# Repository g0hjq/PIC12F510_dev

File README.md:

# PIC12F510_dev

A small and simple PCB design for developing circuits using the PIC12F510 and similar 8-Pin PIC processors.
The processor is 8-pin DIL and may be socketed, all other components are 0805 or SOT23 SMD.

Provides:
* 3 high-current outputs, with on-board LED monitors
* 2 protected inputs with capacitor debounce and pull-ups
* Power Supply Reversal protection
* In-circuit Programming Header
* Access to all PIC Pins

If you don't need all the output or input buffers, there is no need to populate the components

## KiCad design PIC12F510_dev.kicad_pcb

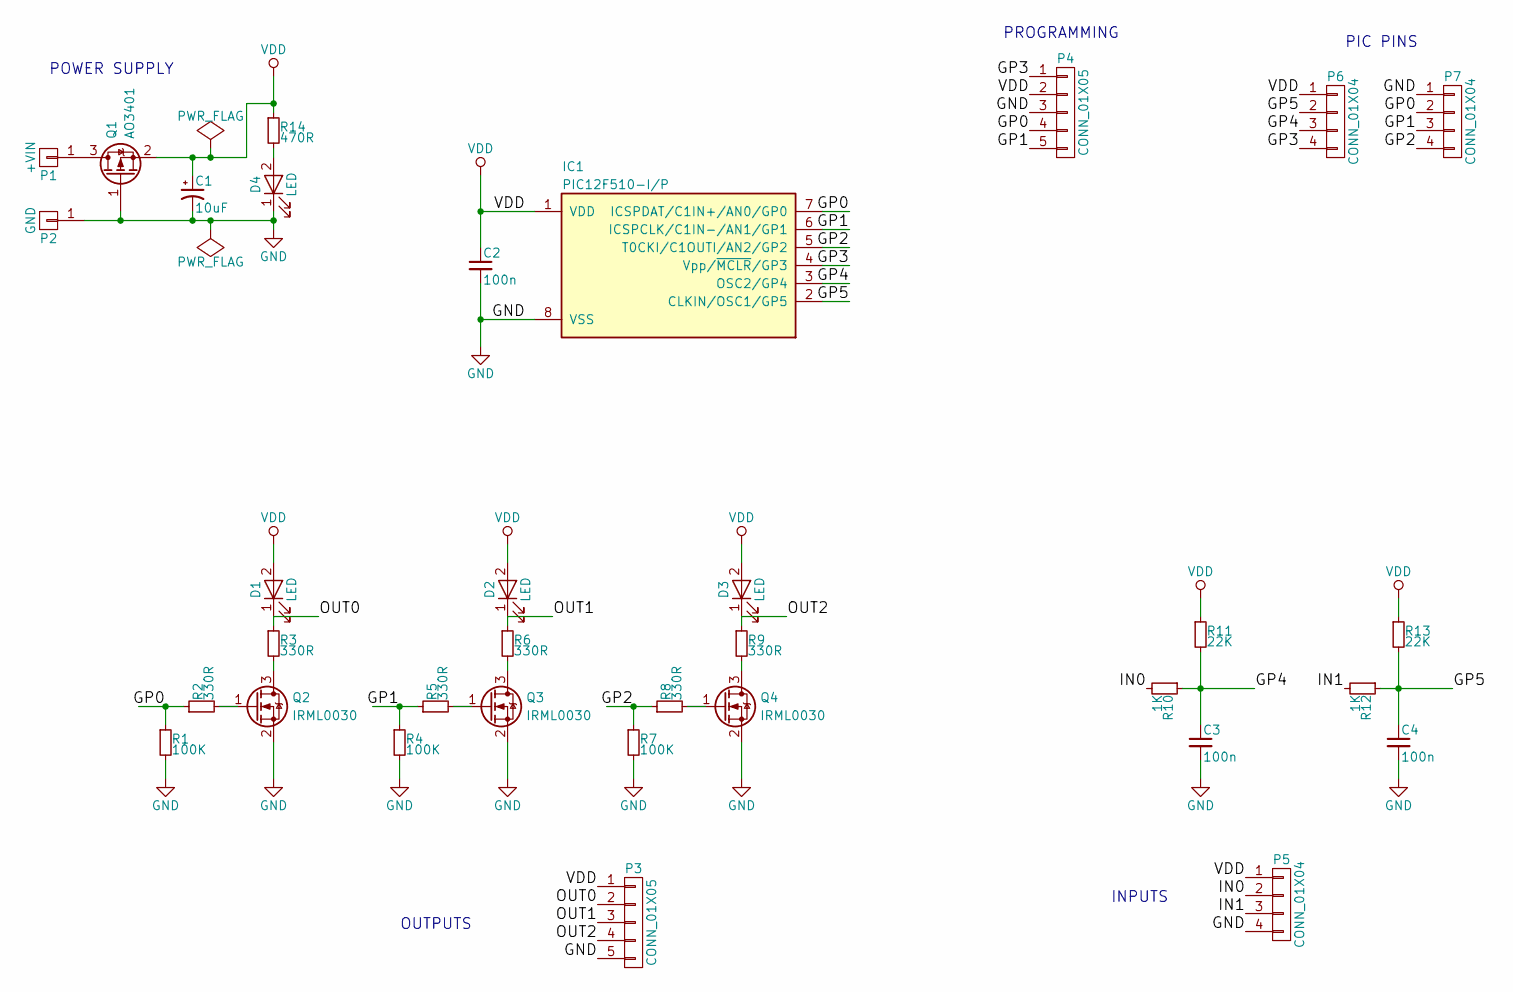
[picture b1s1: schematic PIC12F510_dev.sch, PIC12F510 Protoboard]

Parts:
C1: 10uF; C_0805_HandSoldering
C2, C3, C4: 100n; C_0805_HandSoldering
D1, D2, D3, D4: LED; LED_0805_HandSoldering
IC1: PIC12F510-I/P; DIP-8_W7.62mm
P1: +VIN; Pin_Header_Straight_1x01_Pitch2.54mm
P2: GND; Pin_Header_Straight_1x01_Pitch2.54mm
P3: CONN_01X05; Pin_Header_Straight_1x05_Pitch2.54mm
P4: CONN_01X05; Pin_Header_Angled_1x05_Pitch2.54mm
P5, P6, P7: CONN_01X04; Pin_Header_Straight_1x04_Pitch2.54mm
Q1: AO3401; SOT-23
Q2, Q3, Q4: IRML0030; SOT-23
R1, R4, R7: 100K; R_0805_HandSoldering
R2, R3, R5, R6, R8, R9: 330R; R_0805_HandSoldering
R10, R12: 1K; R_0805_HandSoldering
R11, R13: 22K; R_0805_HandSoldering
R14: 470R; R_0805_HandSoldering

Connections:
/GP0: IC1.7 (ICSPDAT/C1IN+/AN0/GP0), P4.4, P7.2, R1.1, R2.1
/GP1: IC1.6 (ICSPCLK/C1IN-/AN1/GP1), P4.5, P7.3, R4.1, R5.1
/GP2: IC1.5 (T0CKI/C1OUTI/AN2/GP2), P7.4, R7.1, R8.1
/GP3: IC1.4 (Vpp/~MCLR~/GP3), P4.1, P6.4
/GP4: C3.1, IC1.3 (OSC2/GP4), P6.3, R10.1, R11.2
/GP5: C4.1, IC1.2 (CLKIN/OSC1/GP5), P6.2, R12.1, R13.2
/IN0: P5.2, R10.2
/IN1: P5.3, R12.2
/OUT0: D1.1 (K), P3.2, R3.1
/OUT1: D2.1 (K), P3.3, R6.1
/OUT2: D3.1 (K), P3.4, R9.1
GND: C1.2, C2.2, C3.2, C4.2, D4.1 (K), IC1.8 (VSS), P2.1, P3.5, P4.3, P5.4, P7.1, Q1.1 (G), Q2.2 (S), Q3.2 (S), Q4.2 (S), R1.2, R4.2, R7.2
unnamed: D4.2 (A), R14.2
unnamed: P1.1, Q1.3 (D)
unnamed: Q2.1 (G), R2.2
unnamed: Q2.3 (D), R3.2
unnamed: Q3.1 (G), R5.2
unnamed: Q3.3 (D), R6.2
unnamed: Q4.1 (G), R8.2
unnamed: Q4.3 (D), R9.2
VDD: C1.1, C2.1, D1.2 (A), D2.2 (A), D3.2 (A), IC1.1 (VDD), P3.1, P4.2, P5.1, P6.1, Q1.2 (S), R11.1, R13.1, R14.1

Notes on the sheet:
POWER SUPPLY
INPUTS
OUTPUTS
PROGRAMMING
PIC PINS

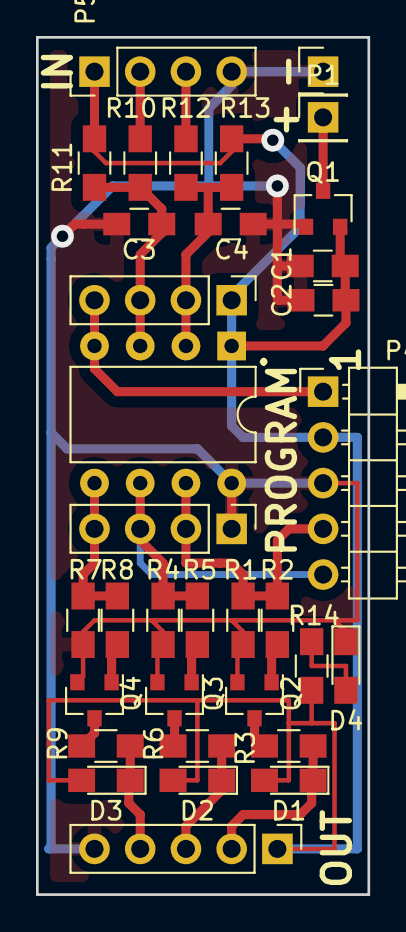
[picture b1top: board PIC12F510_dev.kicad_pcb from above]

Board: 2 copper layers, 18.4 x 47.6 mm, 34 parts (0 on the bottom side), 21 nets.

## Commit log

2018-03-17 Corrected Markdown syntax
